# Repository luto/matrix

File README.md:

# matrix

prototype for a LED matrix with touch input for each individual LED.

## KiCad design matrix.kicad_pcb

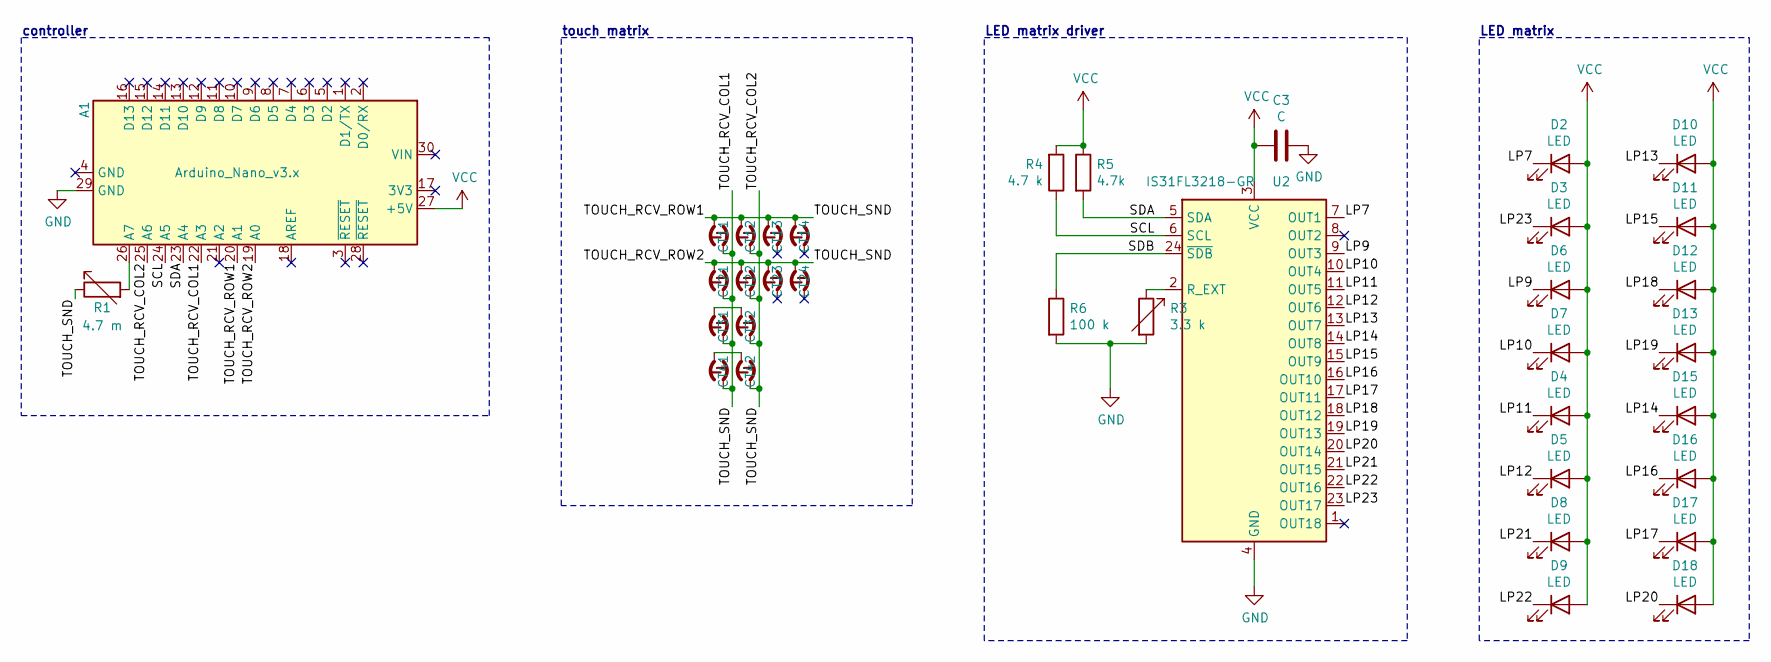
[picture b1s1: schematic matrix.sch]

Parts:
A1: Arduino_Nano_v3.x; Arduino_Nano_Half
C3: C; C_0805_2012Metric
CT11, CT12, CT13, CT14, CT21, CT22, CT23, CT24, CT31, CT32, CT41, CT42: CAPTOUCH; CAPTOUCH-CIRCLE-HOLE-DUAL
D2, D3, D4, D5, D6, D7, D8, D9, D10, D11, D12, D13, D15, D16, D17, D18: LED; AA3528SECKT09
R1: 4.7 m; PinHeader_1x02_P2.54mm_Vertical
R3: 3.3 k; PinHeader_1x02_P2.54mm_Vertical
R4: 4.7 k; R_0805_2012Metric
R5: 4.7k; R_0805_2012Metric
R6: 100 k; R_0805_2012Metric
U2: IS31FL3218-GR; SOP-24_7.5x15.4mm_P1.27mm

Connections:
/LP7: D2.1 (K), U2.7 (OUT1)
/LP9: D6.1 (K), U2.9 (OUT3)
/LP10: D7.1 (K), U2.10 (OUT4)
/LP11: D4.1 (K), U2.11 (OUT5)
/LP12: D5.1 (K), U2.12 (OUT6)
/LP13: D10.1 (K), U2.13 (OUT7)
/LP14: D15.1 (K), U2.14 (OUT8)
/LP15: D11.1 (K), U2.15 (OUT9)
/LP16: D16.1 (K), U2.16 (OUT10)
/LP17: D17.1 (K), U2.17 (OUT11)
/LP18: D12.1 (K), U2.18 (OUT12)
/LP19: D13.1 (K), U2.19 (OUT13)
/LP20: D18.1 (K), U2.20 (OUT14)
/LP21: D8.1 (K), U2.21 (OUT15)
/LP22: D9.1 (K), U2.22 (OUT16)
/LP23: D3.1 (K), U2.23 (OUT17)
/SCL: A1.24 (A5), R4.1, U2.6 (SCL)
/SDA: A1.23 (A4), R5.2, U2.5 (SDA)
/SDB: R6.1, U2.24 (~SDB)
/TOUCH_RCV_COL1: A1.19 (A0), A1.20 (A1), A1.22 (A3), A1.25 (A6), CT11.1, CT11.2, CT12.1, CT12.2, CT13.1, CT14.1, CT21.1, CT21.2, CT22.1, CT22.2, CT23.1, CT24.1, CT31.2, CT32.2, CT41.2, CT42.2, R1.1
GND: A1.29 (GND), C3.1, R3.2, R6.2, U2.4 (GND)
unnamed: A1.26 (A7), R1.2
unnamed: CT31.1, CT32.1
unnamed: CT41.1, CT42.1
unnamed: R3.1, U2.2 (R_EXT)
VCC: A1.27 (+5V), C3.2, D2.2 (A), D3.2 (A), D4.2 (A), D5.2 (A), D6.2 (A), D7.2 (A), D8.2 (A), D9.2 (A), D10.2 (A), D11.2 (A), D12.2 (A), D13.2 (A), D15.2 (A), D16.2 (A), D17.2 (A), D18.2 (A), R4.2, R5.1, U2.3 (VCC)

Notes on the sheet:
LED matrix
LED matrix driver
touch matrix
controller

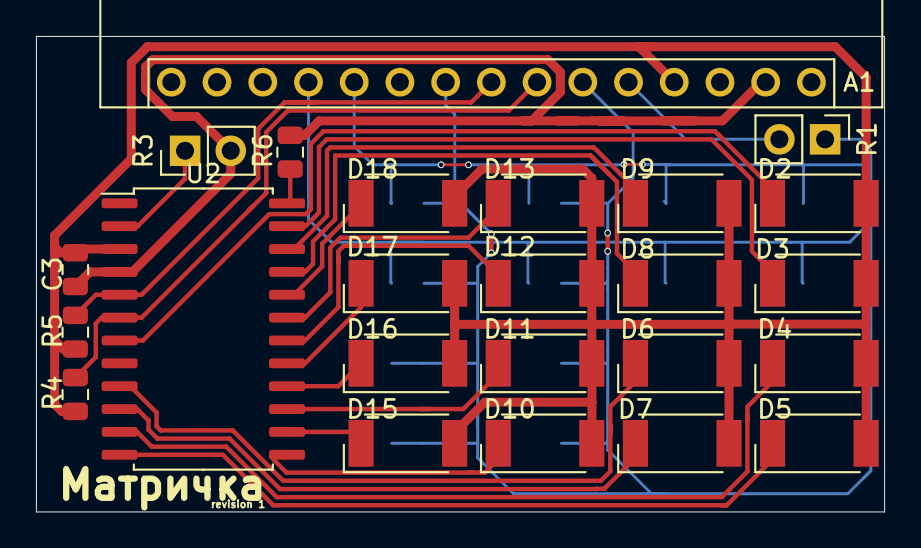
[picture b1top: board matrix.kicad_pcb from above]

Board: 2 copper layers, 47.1 x 26.4 mm, 36 parts (0 on the bottom side), 26 nets.

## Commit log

2020-06-21 add readme
2020-06-21 add name label, shuffle traces
2020-06-22 cleanup
2020-06-24 ready for production
